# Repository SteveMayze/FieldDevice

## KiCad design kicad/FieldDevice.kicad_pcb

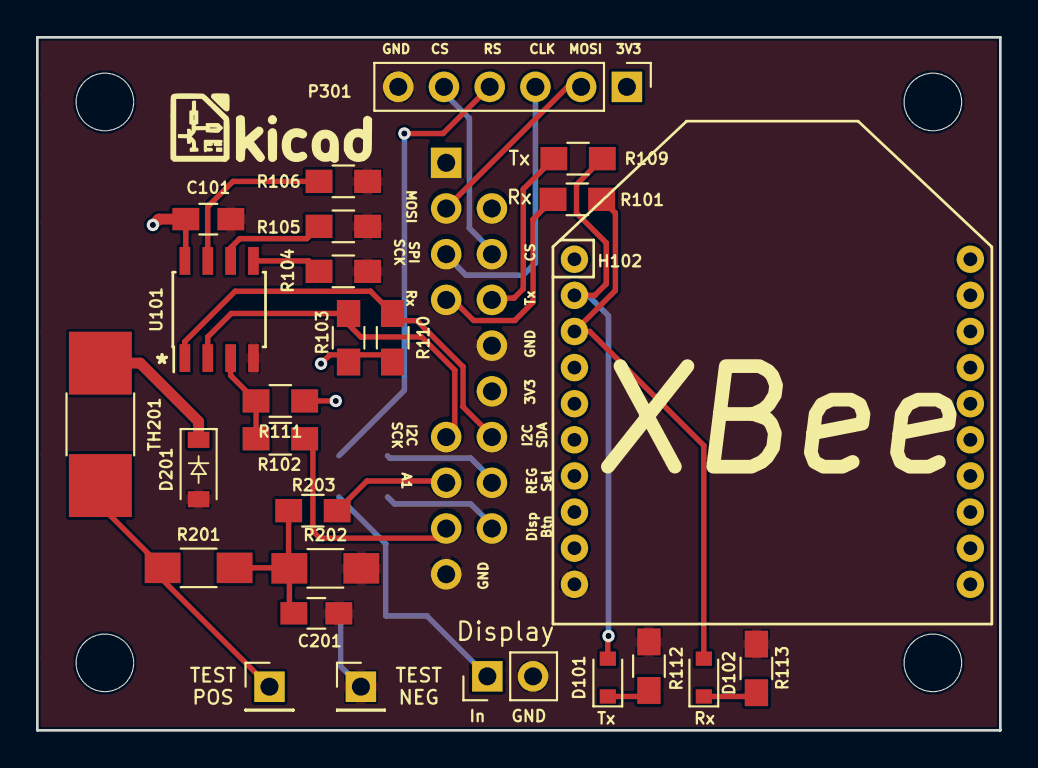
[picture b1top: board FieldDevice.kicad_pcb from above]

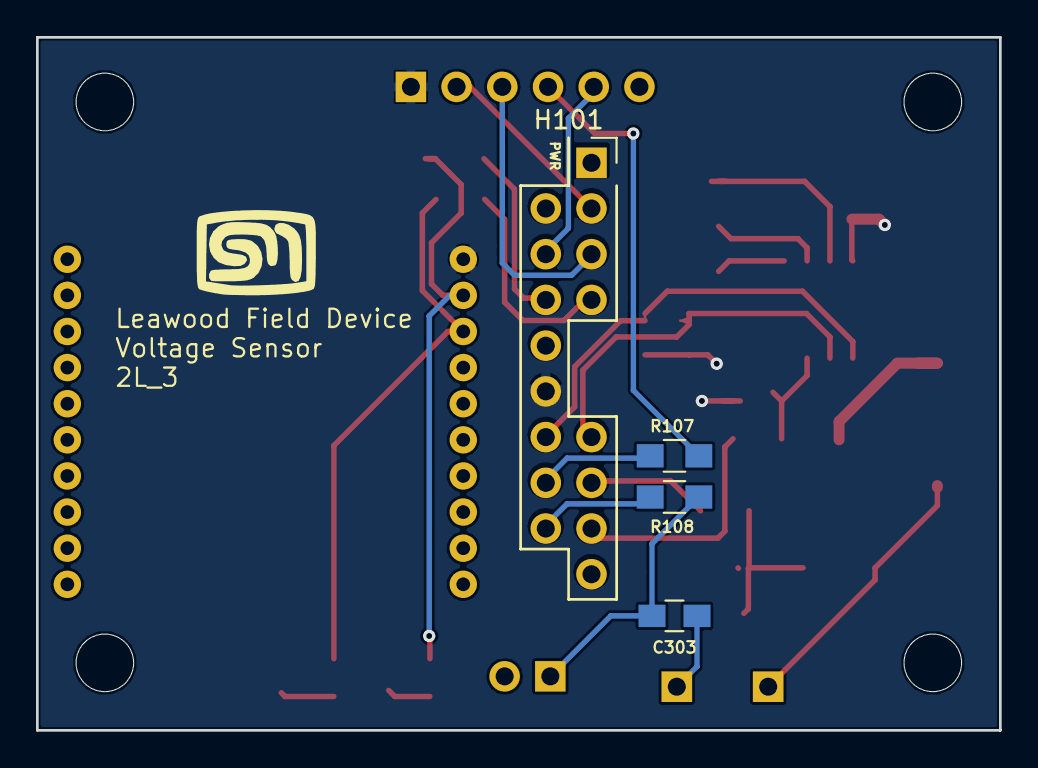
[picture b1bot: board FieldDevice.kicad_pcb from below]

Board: 2 copper layers, 53.5 x 38.5 mm, 30 parts (4 on the bottom side), 26 nets.

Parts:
C101: 100pF 50V; C_0805_HandSoldering
C201: 100nF; C_0805_HandSoldering
C303: 0.1μF; C_0805_HandSoldering
D101, D102: LED; D_0805
D201: 1N4148WFL; D_SOD-123
H101: CE_Socket
H102: DIGI_XBEE; XBEE_S2C
P201: Positive; Pin_Header_Straight_1x01_Pitch2.54mm
P202: Negative; Pin_Header_Straight_1x01_Pitch2.54mm
P301: CONN_01X06; Pin_Header_Straight_1x06_Pitch2.54mm
R101, R102, R107, R108, R203: 0Ω; R_0805_HandSoldering
R103, R110: 4k7Ω; R_0805_HandSoldering
R104, R105, R106, R109: 0; R_0805_HandSoldering
R111: 10k; R_0805_HandSoldering
R112, R113: 680Ω; R_0805_HandSoldering
R201: 1MΩ 125mW 0.1%; R_1206_HandSoldering
R202: 30kΩ 125mW 0.1%; R_1206_HandSoldering
SW301: SW_PUSH; Pin_Header_Straight_1x02_Pitch2.54mm
TH201: 0.50A 15V; R_1812_HandSoldering
U101: DS7505; SOIC-8_3.9x4.9mm_Pitch1.27mm

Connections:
/Analog_Sensors/ANLG_1: H101.15, R203.2
/Analog_Sensors/TEST_POS_1: P201.1, R201.1, TH201.1
/Display/3V3: C101.1, H101.12, H102.1, P301.1, R103.2, R110.2, R111.1, U101.8
/Display/CS: H101.6, P301.5
/Display/Display: C303.2, R108.1, SW301.1
/Display/MOSI: H101.3, P301.2
/Display/RS: P301.4, R107.1
/Display/SPI_SCK: H101.5, P301.3
/I2C_SCK: H101.13, R103.1, U101.2
/OverTemp: R102.2, R111.2, U101.3
/RX: D102.2, H102.3, R101.2
/SDA: H101.14, R110.1, U101.1
/TX: D101.2, H102.2, R109.1
GND: C101.2, C201.2, C303.1, D201.2, H101.10, H101.19, H102.10, P202.1, P301.6, R104.2, R105.2, R106.2, R112.1, R113.1, R202.2, SW301.2, U101.4
unnamed: C201.1, R201.2, R202.1, R203.1
unnamed: D101.1, R112.2
unnamed: D102.1, R113.2
unnamed: D201.1, TH201.2
unnamed: H101.7, R101.1
unnamed: H101.8, R109.2
unnamed: H101.16, R107.2
unnamed: H101.17, R102.1
unnamed: H101.18, R108.2
unnamed: R104.1, U101.5
unnamed: R105.1, U101.6
unnamed: R106.1, U101.7

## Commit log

2017-06-04 Created the KiCad project for the first field module
2017-06-05 Adding more features to the design
2017-06-13 Completed schematic, layout and gerbers. 2L_1
2017-07-06 added the missing pullup resistors 2L_2
2017-08-03 Corrected the usage of the CE_Header to be front-side only
2017-08-09 Change over to use the DOGM081 adapter board rather than direct connect - also used the CE_Socket!
2017-08-13 Testing the idea of a zenner on the V Input. Added test code for the voltage test
2017-08-13 Created a small spreadsheet to record the voltage tester results
2017-08-15 Some changes to the test firmware and removed the Zenner
2017-08-19 Small formatting changes on schematic for Forum questions
2017-10-05 Enhanced display port connector and layout - Submit to OSH Park
2017-10-19 Added test code to drive the LCD display
2018-01-06 Started to implement the driver for the DOGS104 display
2018-01-08 Working on the DOGS104 display driver
2018-01-10 Reshuffled the firmware to keep the dogs081 driver
2018-01-10 Started to clean up the drivers for the respective displays
2018-01-10 Altered the display connector for the DOG104 i.e. general purpose
2018-01-11 Modularised the display code
2018-01-28 Revamping the schematic and layout for a deployable model
2018-01-28 Added a driver for the DOGS104 Display
2018-01-30 Reworking the schematic
2018-02-01 Completed the new schematic (draft) and started the layout to verify the design
2018-02-03 Completed the draft of REV2
2018-02-03 More changes to the layout for the Power System integration
2018-02-03 Removing the 3d model for the teensy
2018-02-26 Reduced the number of sends by testing changes in the Voltage only
2018-03-10 Small changes to the firmware to display msg status on the display
2018-03-10 Added the attitional analog input for backup battery monitor - TBC
2018-04-02 Firmware updates
2018-04-28 Branch the XBee_Display_1 (ported from master) to create the better firmwware for this hardware release
2018-04-30 Small adjustments to the timing and messages
2018-04-30 Added some extra diagnostics for verifying the reading to voltage coeficient.
2018-05-21 Adjusts the calibration of the voltage divider for 14V and optimises the display update
2018-05-21 Still more configuration
2018-07-01 Created the package for the OSH Stencils
2018-08-19 Started some changes to model a tank for a demo
2019-01-10 Test tank example
2019-01-11 Altered the capacity coef
